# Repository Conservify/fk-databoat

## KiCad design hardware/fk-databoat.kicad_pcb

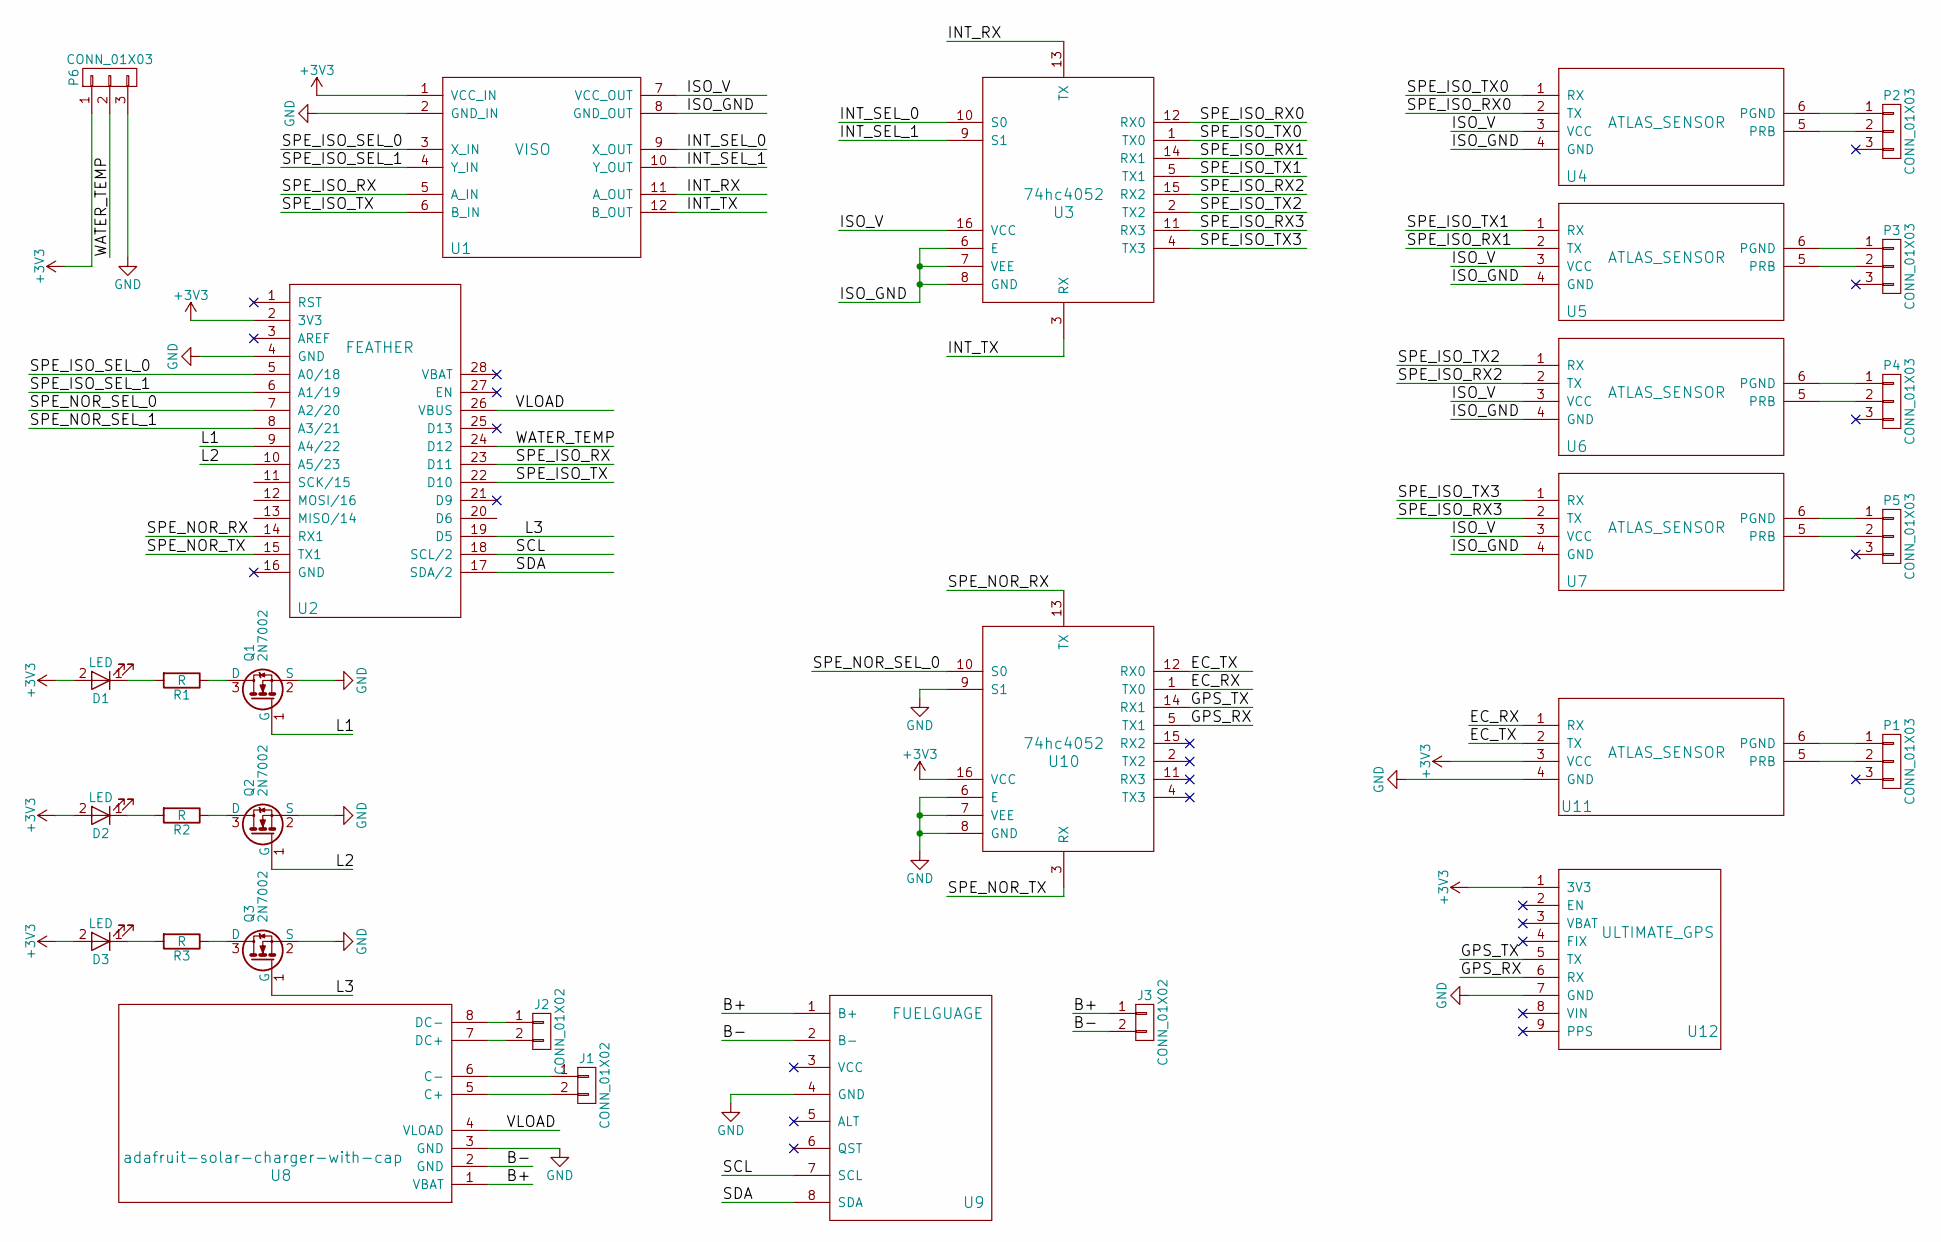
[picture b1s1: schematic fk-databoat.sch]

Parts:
D1, D2, D3: LED; R_0603_HandSoldering
J1, J2: CONN_01X02; Socket_Strip_Straight_1x02_Pitch2.54mm
J3: CONN_01X02; JST_PH_S2B-PH-SM4-TB_02x2.00mm_Angled
P1, P2, P3, P4, P5, P6: CONN_01X03; Socket_Strip_Straight_1x03_Pitch2.54mm
Q1, Q2, Q3: 2N7002; SOT-23
R1, R2, R3: R; R_0603_HandSoldering
U1: VISO; voltage_isolator
U2: FEATHER; feather
U3, U10: 74hc4052; SOIC-16_3.9x9.9mm_Pitch1.27mm
U4, U5, U6, U7, U11: ATLAS_SENSOR; atlas_sensor_board
U8: adafruit-solar-charger-with-cap
U9: FUELGUAGE; fuelgauge
U12: ULTIMATE_GPS; Socket_Strip_Straight_1x09_Pitch2.54mm

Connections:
+3V3: D1.2 (A), D2.2 (A), D3.2 (A), P6.1, U1.1 (VCC_IN), U2.2 (3V3), U10.16 (VCC), U11.3 (VCC), U12.1 (3V3)
/B+: J3.1, U8.1 (VBAT), U9.1 (B+)
/B-: J3.2, U8.2 (GND), U9.2 (B-)
/EC_RX: U10.1 (TX0), U11.1 (RX)
/EC_TX: U10.12 (RX0), U11.2 (TX)
/GPS_RX: U10.5 (TX1), U12.6 (RX)
/GPS_TX: U10.14 (RX1), U12.5 (TX)
/INT_RX: U1.11 (A_OUT), U3.13 (TX)
/INT_SEL_0: U1.9 (X_OUT), U3.10 (S0)
/INT_SEL_1: U1.10 (Y_OUT), U3.9 (S1)
/INT_TX: U1.12 (B_OUT), U3.3 (RX)
/ISO_GND: U1.8 (GND_OUT), U3.6 (E), U3.7 (VEE), U3.8 (GND), U4.4 (GND), U5.4 (GND), U6.4 (GND), U7.4 (GND)
/ISO_V: U1.7 (VCC_OUT), U3.16 (VCC), U4.3 (VCC), U5.3 (VCC), U6.3 (VCC), U7.3 (VCC)
/L1: Q1.1 (G), U2.9 (A4/22)
/L2: Q2.1 (G), U2.10 (A5/23)
/L3: Q3.1 (G), U2.19 (D5)
/SCL: U2.18 (SCL/2), U9.7 (SCL)
/SDA: U2.17 (SDA/2), U9.8 (SDA)
/SPE_ISO_RX: U1.5 (A_IN), U2.23 (D11)
/SPE_ISO_RX0: U3.12 (RX0), U4.2 (TX)
/SPE_ISO_RX1: U3.14 (RX1), U5.2 (TX)
/SPE_ISO_RX2: U3.15 (RX2), U6.2 (TX)
/SPE_ISO_RX3: U3.11 (RX3), U7.2 (TX)
/SPE_ISO_SEL_0: U1.3 (X_IN), U2.5 (A0/18)
/SPE_ISO_SEL_1: U1.4 (Y_IN), U2.6 (A1/19)
/SPE_ISO_TX: U1.6 (B_IN), U2.22 (D10)
/SPE_ISO_TX0: U3.1 (TX0), U4.1 (RX)
/SPE_ISO_TX1: U3.5 (TX1), U5.1 (RX)
/SPE_ISO_TX2: U3.2 (TX2), U6.1 (RX)
/SPE_ISO_TX3: U3.4 (TX3), U7.1 (RX)
/SPE_NOR_RX: U2.14 (RX1), U10.13 (TX)
/SPE_NOR_SEL_0: U2.7 (A2/20), U10.10 (S0)
/SPE_NOR_SEL_1: U2.8 (A3/21)
/SPE_NOR_TX: U2.15 (TX1), U10.3 (RX)
/VLOAD: U2.26 (VBUS), U8.4 (VLOAD)
/WATER_TEMP: P6.2, U2.24 (D12)
GND: P6.3, Q1.2 (S), Q2.2 (S), Q3.2 (S), U1.2 (GND_IN), U2.4 (GND), U8.3 (GND), U9.4 (GND), U10.6 (E), U10.7 (VEE), U10.8 (GND), U10.9 (S1), U11.4 (GND), U12.7 (GND)
unnamed: D1.1 (K), R1.2
unnamed: D2.1 (K), R2.2
unnamed: D3.1 (K), R3.2
unnamed: J1.1, U8.6 (C-)
unnamed: J1.2, U8.5 (C+)
unnamed: J2.1, U8.8 (DC-)
unnamed: J2.2, U8.7 (DC+)
unnamed: P1.1, U11.6 (PGND)
unnamed: P1.2, U11.5 (PRB)
unnamed: P2.1, U4.6 (PGND)
unnamed: P2.2, U4.5 (PRB)
unnamed: P3.1, U5.6 (PGND)
unnamed: P3.2, U5.5 (PRB)
unnamed: P4.1, U6.6 (PGND)
unnamed: P4.2, U6.5 (PRB)
unnamed: P5.1, U7.6 (PGND)
unnamed: P5.2, U7.5 (PRB)
unnamed: Q1.3 (D), R1.1
unnamed: Q2.3 (D), R2.1
unnamed: Q3.3 (D), R3.1

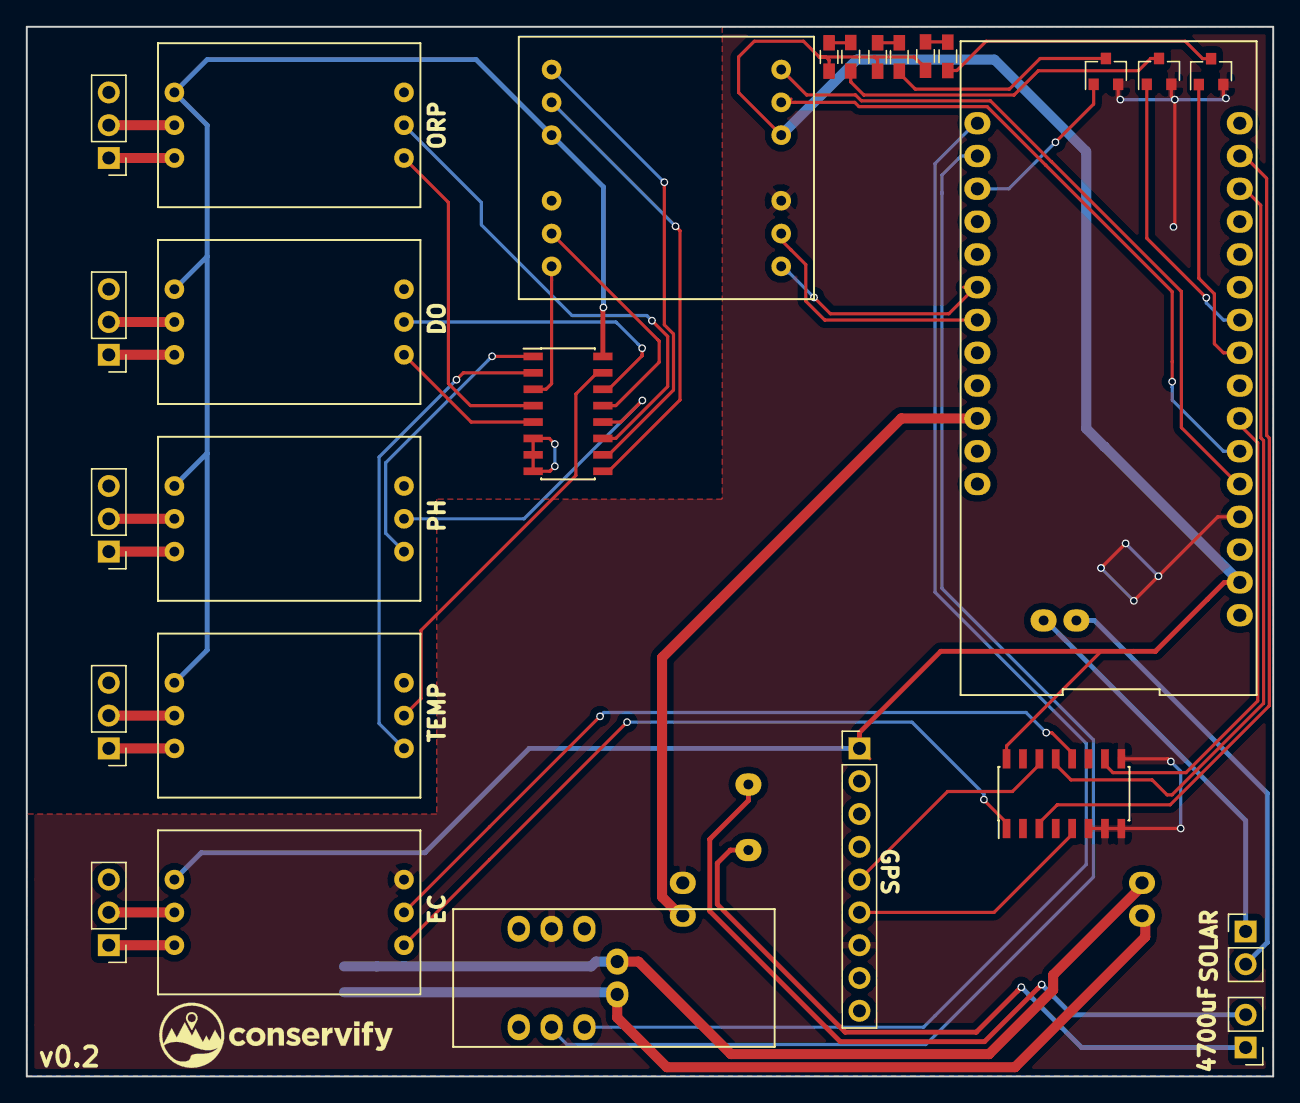
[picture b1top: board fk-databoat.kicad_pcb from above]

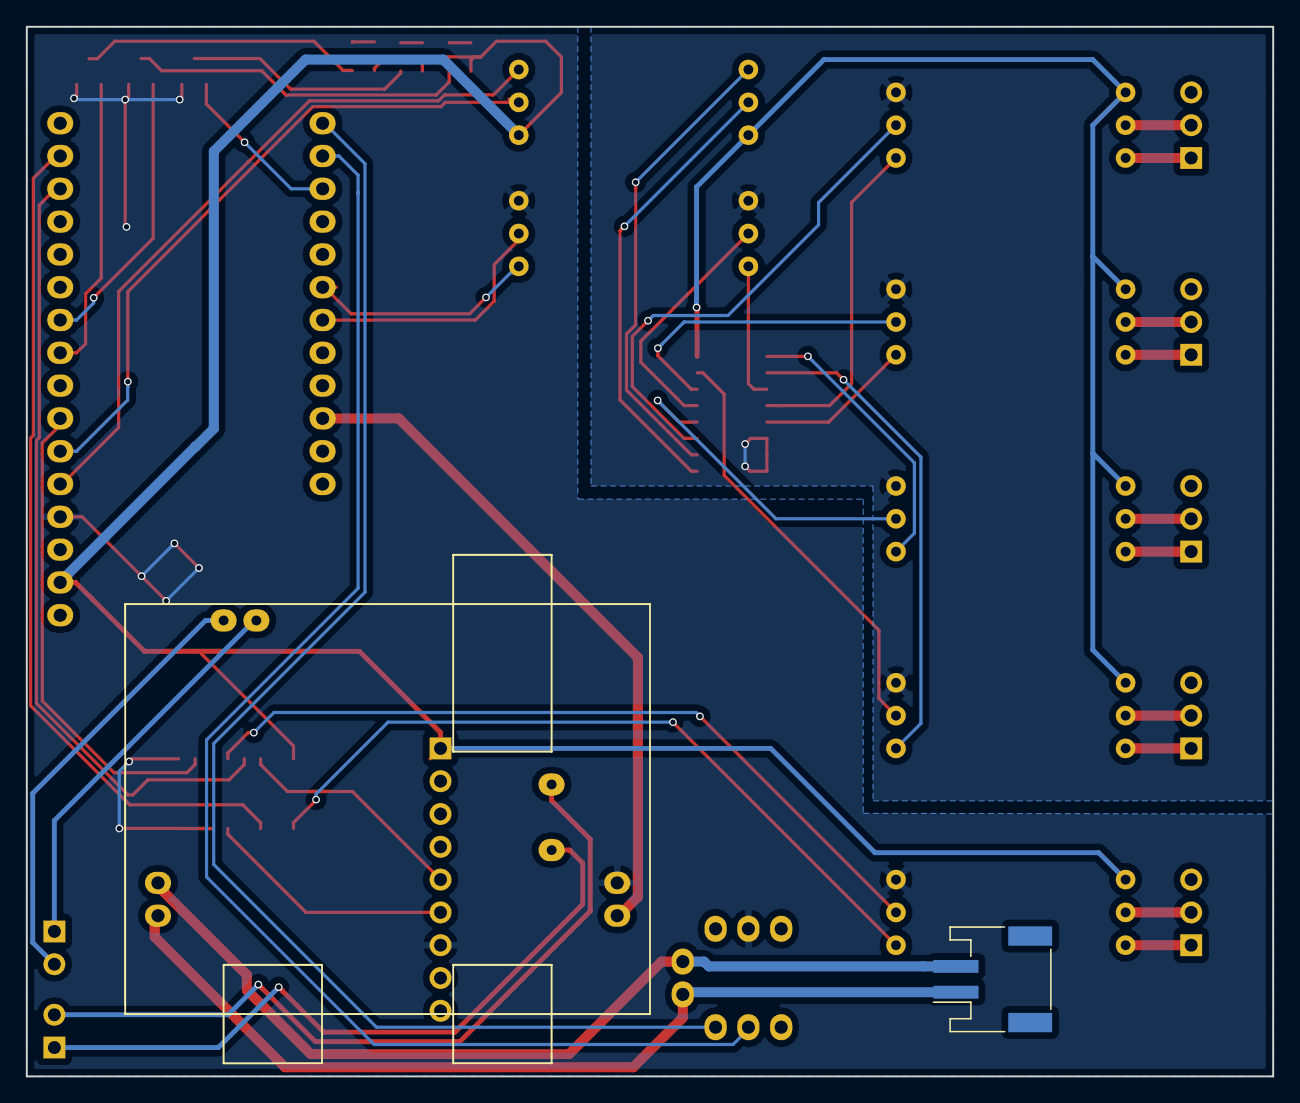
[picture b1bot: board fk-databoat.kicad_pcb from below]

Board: 2 copper layers, 96.5 x 81.3 mm, 29 parts (2 on the bottom side), 55 nets.

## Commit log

2017-04-14 First pass at a quick databoat board.
2017-04-15 Starting to lay down traces.
2017-04-17 More routing/laying out.
2017-04-17 Last of the routing. Gonna do the cap on the solar charger now.
2017-04-17 Add solar charger that pulls out some connections to slim things up.
2017-04-17 Plotting.
2017-04-27 Fix E and S1 GND issues on SPE. Add logo/version.
2017-06-10 Fixing GPS orientation.
2017-06-19 Integrate serial port expander into data boat PCB.
